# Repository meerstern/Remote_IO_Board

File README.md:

# リモートIO基板
# Remote IO Board
Remote IO Board with Shift Register 

## 概要 
  * 本基板はIO信号をシリアル化してメイン基板とサブ基板間で同期する基板です  
  * メイン基板、サブ基板ともにそれぞれ8本の入力と出力を備えており、メイン基板とサブ基盤間で各信号のON/OFF状態が同期されます
  * 本基板はマイコンやFPGA等を使用せず、シフトレジスタ、タイマ、カウンタ等のICのみで構成されています  
  * ボタンやLED等のユーザ入出力の配線を省配線化する際に便利です  
  * 本基板を使用せずに8入力/8出力の信号をそのまま伝送すると一般的には計16本の信号線が必要となります  
  * 本基板を使用すると信号線3本のみで伝送することが可能です（同期クロック＋シリアルデータx2、電源線除く）
  * 本基板を使用すると電源線を含めても計5本の配線で双方向に8入力/8出力の信号を伝送できます  
  * 片方向のみの場合は信号線2本のみで伝送することが可能です（同期クロック＋シリアルデータx1※D0 or D1を未接続、電源線除く）  
  * 各入出力の動作確認用にそれぞれボタン及びLEDを備えています
  * 例えば、操作盤と制御盤が離れている場合に操作盤と制御盤間の省配線化が可能になります

## 仕様
  * 電源電圧DC2V~5.5V  
  * メイン基板とサブ基板でそれぞれ8入力/8出力  
  * メイン基板とサブ基板の電源は同一の電源電圧を供給してください  
  * 約1kHzの周期で双方向に同期します(内部クロック約8kHz、8bit+同期1bit)
  * 入力に74HC165、出力に74HC595を使用しているため、シリアル転送中に変換途中の信号出力を防止しています    
  * 入力ポートは基板内部でプルダウンされています  
  * メイン基板とサブ基板の伝送距離は最大数m程度を想定しています
  * メイン基板外形47.5mm x 38mm, M3x2(穴幅41mm)
  * サブ基板外形41.5mm x38mm, M3x2(穴幅35mm)

## 使用方法
  * 出荷時はメイン基板とサブ基板が一体になっています　　
  * 基板にはミシン目（スリット）が入っていますので必要に応じてカットして使用してください　　
  * メイン基板とサブ基板のSCK同士、D0同士、D1同士をケーブルで接続します  
  * 片方向のみで使用する場合はD0もしくはD1のどちらかを未接続で使用します  
  * メイン基板とサブ基板のVCCとGNDに電源を接続します 
  * 必要に応じてIN0-15にスイッチ、OUT0-15にLED等を配線してください  
  * 基板内部でプルダウンされているため、未使用の入力は未接続で使用します  

## 注意 
  * ON/OFFのデジタル信号が同期されます。アナログ信号の同期はできません  
  * 電源投入直後は同期状態や出力が不安定な場合があります  
  * 伝送距離が長い場合やノイズ環境下等では信号同期が安定しない場合があります  
  * ノイズ環境下や長い伝送距離の場合は必要に応じて、シールドケーブルやフォトカプラ等でノイズ対策を追加してください  
  * 高い信頼性が求められる用途には使用しないでください    
  * メイン基板とサブ基板は必要に応じて分離して使用してください  
  * 分離の際や分離後のエッジ部分は鋭利なため、怪我をしないように注意してください    
  * 基板をカットする際はそれぞれの基板に過大な力が掛からない様にして下さい　　

※LEDが高速に点滅しているように見えますが、実際はスイッチ状態に応じて点灯しています  

MIT Lisense

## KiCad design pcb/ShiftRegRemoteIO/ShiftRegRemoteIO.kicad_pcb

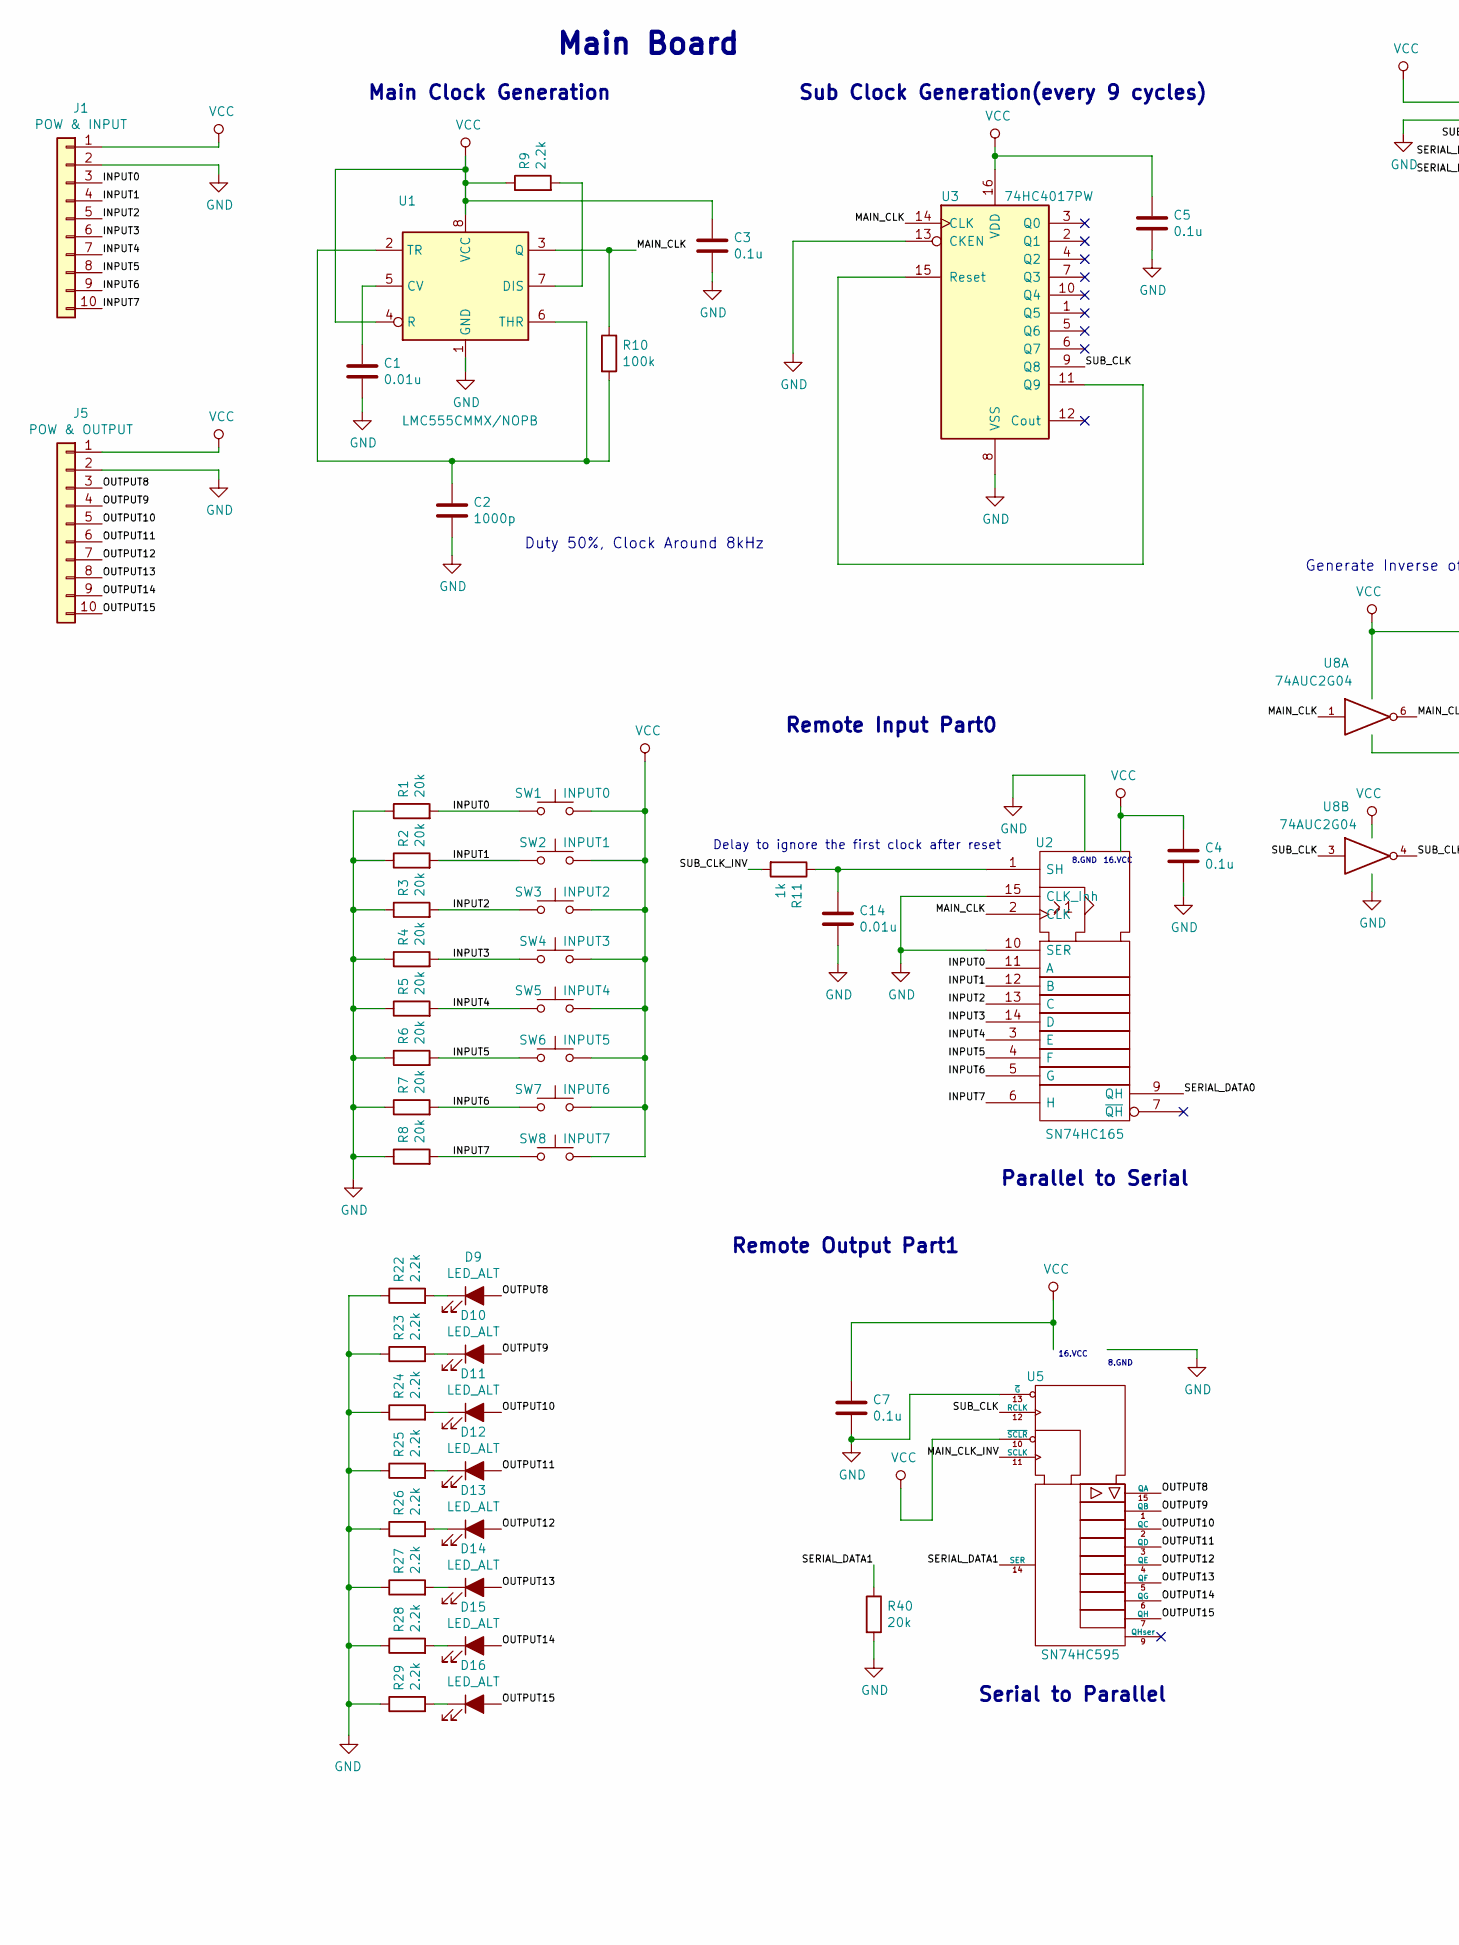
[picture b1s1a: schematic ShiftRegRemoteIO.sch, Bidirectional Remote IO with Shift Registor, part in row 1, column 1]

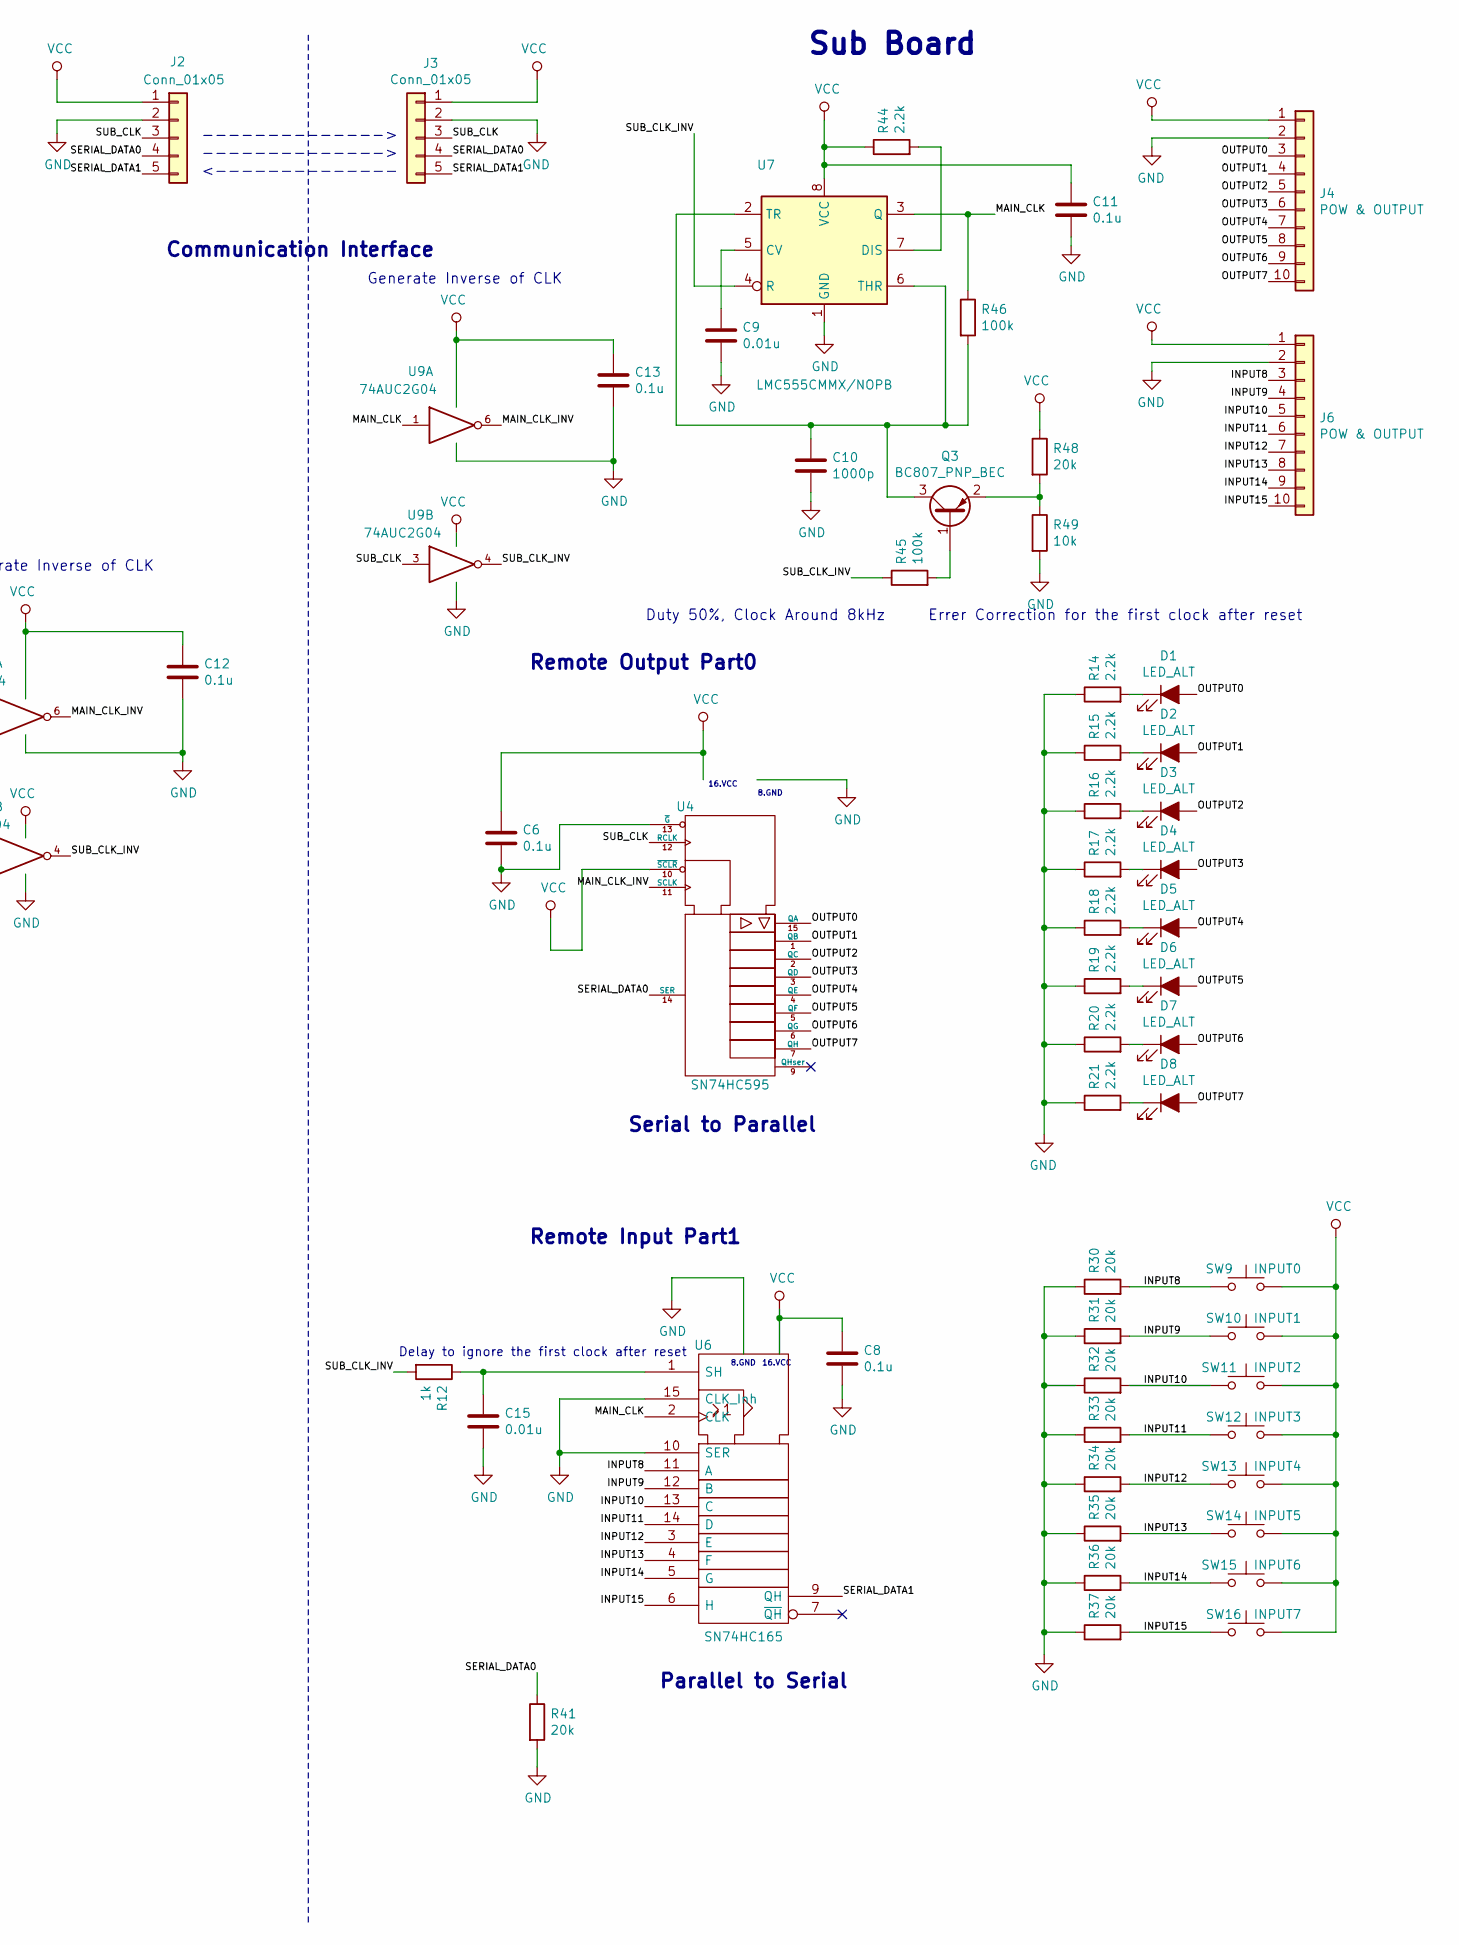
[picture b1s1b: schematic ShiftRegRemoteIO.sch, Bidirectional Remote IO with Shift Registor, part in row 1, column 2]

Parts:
C1, C9, C14, C15: 0.01u; C_0603_1608Metric
C2, C10: 1000p; C_0603_1608Metric
C3, C4, C5, C6, C7, C8, C11, C12, C13: 0.1u; C_0603_1608Metric
D1, D2, D3, D4, D5, D6, D7, D8, D9, D10, D11, D12, D13, D14, D15, D16: LED_ALT; LED_0603_1608Metric
J1: POW & INPUT; PinHeader_1x10_P2.54mm_Vertical
J2, J3: Conn_01x05; PinHeader_1x05_P2.54mm_Vertical
J4, J5, J6: POW & OUTPUT; PinHeader_1x10_P2.54mm_Vertical
Q3: BC807_PNP_BEC; SOT-23
R1, R2, R3, R4, R5, R6, R7, R8, R30, R31, R32, R33, R34, R35, R36, R37, R40, R41, R48: 20k; R_0603_1608Metric
R9, R14, R15, R16, R17, R18, R19, R20, R21, R22, R23, R24, R25, R26, R27, R28, R29, R44: 2.2k; R_0603_1608Metric
R10, R45, R46: 100k; R_0603_1608Metric
R11, R12: 1k; R_0603_1608Metric
R49: 10k; R_0603_1608Metric
SW1, SW9: INPUT0; SKRPACE010
SW2, SW10: INPUT1; SKRPACE010
SW3, SW11: INPUT2; SKRPACE010
SW4, SW12: INPUT3; SKRPACE010
SW5, SW13: INPUT4; SKRPACE010
SW6, SW14: INPUT5; SKRPACE010
SW7, SW15: INPUT6; SKRPACE010
SW8, SW16: INPUT7; SKRPACE010
U1, U7: LMC555CMMX/NOPB; TSSOP-8_3x3mm_P0.65mm
U2, U6: SN74HC165; SSOP-16_3.9x4.9mm_P0.635mm
U3: 74HC4017PW; SSOP-16_3.9x4.9mm_P0.635mm
U4, U5: SN74HC595; SSOP-16_3.9x4.9mm_P0.635mm
U8, U9: 74AUC2G04; SOT-23-6

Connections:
/INPUT0: J1.3, R1.2, SW1.1, U2.11 (A)
/INPUT1: J1.4, R2.2, SW2.1, U2.12 (B)
/INPUT2: J1.5, R3.2, SW3.1, U2.13 (C)
/INPUT3: J1.6, R4.2, SW4.1, U2.14 (D)
/INPUT4: J1.7, R5.2, SW5.1, U2.3 (E)
/INPUT5: J1.8, R6.2, SW6.1, U2.4 (F)
/INPUT6: J1.9, R7.2, SW7.1, U2.5 (G)
/INPUT7: J1.10, R8.2, SW8.1, U2.6 (H)
/INPUT8: J6.3, R30.2, SW9.1, U6.11 (A)
/INPUT9: J6.4, R31.2, SW10.1, U6.12 (B)
/INPUT10: J6.5, R32.2, SW11.1, U6.13 (C)
/INPUT11: J6.6, R33.2, SW12.1, U6.14 (D)
/INPUT12: J6.7, R34.2, SW13.1, U6.3 (E)
/INPUT13: J6.8, R35.2, SW14.1, U6.4 (F)
/INPUT14: J6.9, R36.2, SW15.1, U6.5 (G)
/INPUT15: J6.10, R37.2, SW16.1, U6.6 (H)
/MAIN_CLK: R10.1, R46.1, U1.3 (Q), U2.2 (CLK), U3.14 (CLK), U6.2 (CLK), U7.3 (Q), U8.1, U9.1
/MAIN_CLK_INV: U4.11 (SCLK), U5.11 (SCLK), U8.6, U9.6
/OUTPUT0: D1.2 (A), J4.3, U4.15 (QA)
/OUTPUT1: D2.2 (A), J4.4, U4.1 (QB)
/OUTPUT2: D3.2 (A), J4.5, U4.2 (QC)
/OUTPUT3: D4.2 (A), J4.6, U4.3 (QD)
/OUTPUT4: D5.2 (A), J4.7, U4.4 (QE)
/OUTPUT5: D6.2 (A), J4.8, U4.5 (QF)
/OUTPUT6: D7.2 (A), J4.9, U4.6 (QG)
/OUTPUT7: D8.2 (A), J4.10, U4.7 (QH)
/OUTPUT8: D9.2 (A), J5.3, U5.15 (QA)
/OUTPUT9: D10.2 (A), J5.4, U5.1 (QB)
/OUTPUT10: D11.2 (A), J5.5, U5.2 (QC)
/OUTPUT11: D12.2 (A), J5.6, U5.3 (QD)
/OUTPUT12: D13.2 (A), J5.7, U5.4 (QE)
/OUTPUT13: D14.2 (A), J5.8, U5.5 (QF)
/OUTPUT14: D15.2 (A), J5.9, U5.6 (QG)
/OUTPUT15: D16.2 (A), J5.10, U5.7 (QH)
/SERIAL_DATA0: J2.4, J3.4, R41.1, U2.9 (QH), U4.14 (SER)
/SERIAL_DATA1: J2.5, J3.5, R40.1, U5.14 (SER), U6.9 (QH)
/SUB_CLK: J2.3, J3.3, U3.9 (Q8), U4.12 (RCLK), U5.12 (RCLK), U8.3, U9.3
/SUB_CLK_INV: R11.2, R12.2, R45.1, U7.4 (R), U8.4, U9.4
GND: C1.2, C2.2, C3.2, C4.2, C5.2, C6.2, C7.2, C8.2, C9.2, C10.2, C11.2, C12.2, C13.2, C14.2, C15.2, J1.2, J2.2, J3.2, J4.2, J5.2, J6.2, R1.1, R2.1, R3.1, R4.1, R5.1, R6.1, R7.1, R8.1, R14.1, R15.1, R16.1, R17.1, R18.1, R19.1, R20.1, R21.1, R22.1, R23.1, R24.1, R25.1, R26.1, R27.1, R28.1, R29.1, R30.1, R31.1, R32.1, R33.1, R34.1, R35.1, R36.1, R37.1, R40.2, R41.2, R49.2, U1.1 (GND), U2.8 (GND), U2.10 (SER), U2.15 (CLK_Inh), U3.8 (VSS), U3.13 (CKEN), U4.8 (GND), U4.13 (~G), U5.8 (GND), U5.13 (~G), U6.8 (GND), U6.10 (SER), U6.15 (CLK_Inh), U7.1 (GND), U8.2 (GND), U9.2 (GND)
unnamed: C1.1, U1.5 (CV)
unnamed: C2.1, R10.2, U1.2 (TR), U1.6 (THR)
unnamed: C9.1, U7.5 (CV)
unnamed: C10.1, Q3.3 (C), R46.2, U7.2 (TR), U7.6 (THR)
unnamed: C14.1, R11.1, U2.1 (SH)
unnamed: C15.1, R12.1, U6.1 (SH)
unnamed: D1.1 (K), R14.2
unnamed: D2.1 (K), R15.2
unnamed: D3.1 (K), R16.2
unnamed: D4.1 (K), R17.2
unnamed: D5.1 (K), R18.2
unnamed: D6.1 (K), R19.2
unnamed: D7.1 (K), R20.2
unnamed: D8.1 (K), R21.2
unnamed: D9.1 (K), R22.2
unnamed: D10.1 (K), R23.2
unnamed: D11.1 (K), R24.2
unnamed: D12.1 (K), R25.2
unnamed: D13.1 (K), R26.2
unnamed: D14.1 (K), R27.2
unnamed: D15.1 (K), R28.2
unnamed: D16.1 (K), R29.2
unnamed: Q3.1 (B), R45.2
unnamed: Q3.2 (E), R48.2, R49.1
unnamed: R9.2, U1.7 (DIS)
unnamed: R44.2, U7.7 (DIS)
unnamed: U3.11 (Q9), U3.15 (Reset)
VCC: C3.1, C4.1, C5.1, C6.1, C7.1, C8.1, C11.1, C12.1, C13.1, J1.1, J2.1, J3.1, J4.1, J5.1, J6.1, R9.1, R44.1, R48.1, SW1.2, SW2.2, SW3.2, SW4.2, SW5.2, SW6.2, SW7.2, SW8.2, SW9.2, SW10.2, SW11.2, SW12.2, SW13.2, SW14.2, SW15.2, SW16.2, U1.4 (R), U1.8 (VCC), U2.16 (VCC), U3.16 (VDD), U4.10 (~SCLR), U4.16 (VCC), U5.10 (~SCLR), U5.16 (VCC), U6.16 (VCC), U7.8 (VCC), U8.5 (VCC), U9.5 (VCC)

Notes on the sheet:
Main Clock Generation
Sub Clock Generation(every 9 cycles)
Parallel to Serial
Duty 50%, Clock Around 8kHz
Communication Interface
Serial to Parallel
Generate Inverse of CLK
Remote Input Part0
Remote Output Part0
16.VCC
8.GND
Remote Output Part1
Remote Input Part1
Errer Correction for the first clock after reset
Sub Board
Main Board
Delay to ignore the first clock after reset
-------------->
<--------------

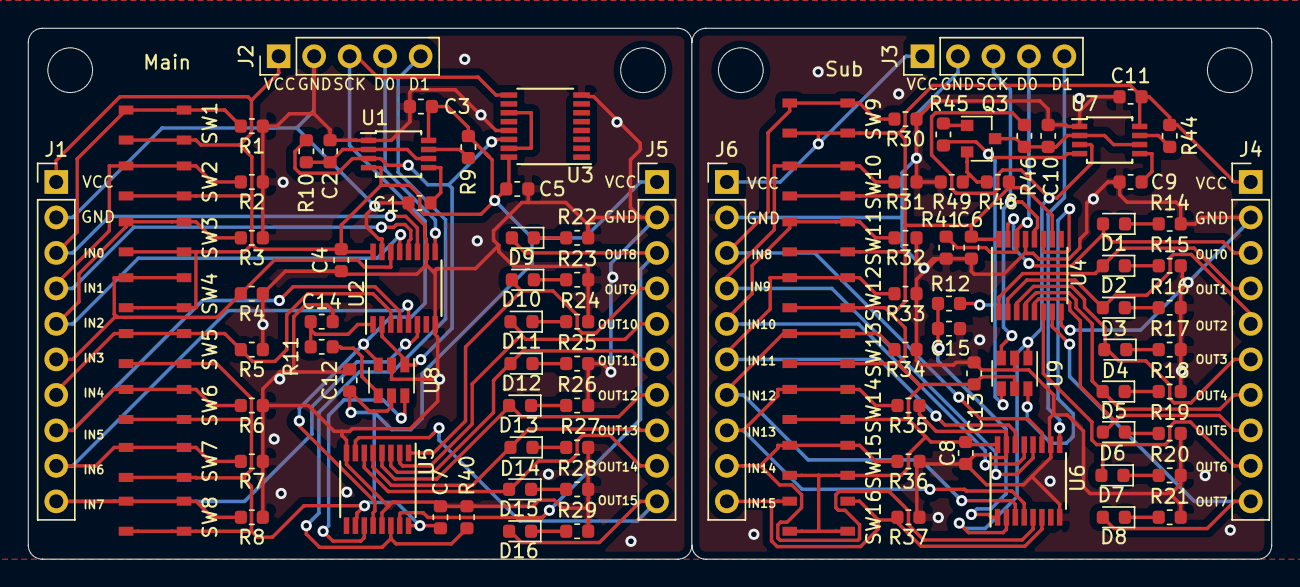
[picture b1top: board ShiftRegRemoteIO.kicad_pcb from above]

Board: 2 copper layers, 89.0 x 38.0 mm, 110 parts (0 on the bottom side), 67 nets.

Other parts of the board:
REF1, REF2, REF3, REF4: MountingHole_3.2mm_M3

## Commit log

2025-05-24 Add files
2025-05-24 Fix image
2025-05-24 Add gif
